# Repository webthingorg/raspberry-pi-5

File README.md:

📸 Raspberry Pi 5 Hardware

## Pictures

## Schematic

[PDF](raspberry-pi-5.pdf)

## Bill Of Materials

[Interactive BOM](https://gitlab.com/webthing.org/raspberry-pi-5/-/raw/main/raspberry-pi-5-bom.html?inline=false)

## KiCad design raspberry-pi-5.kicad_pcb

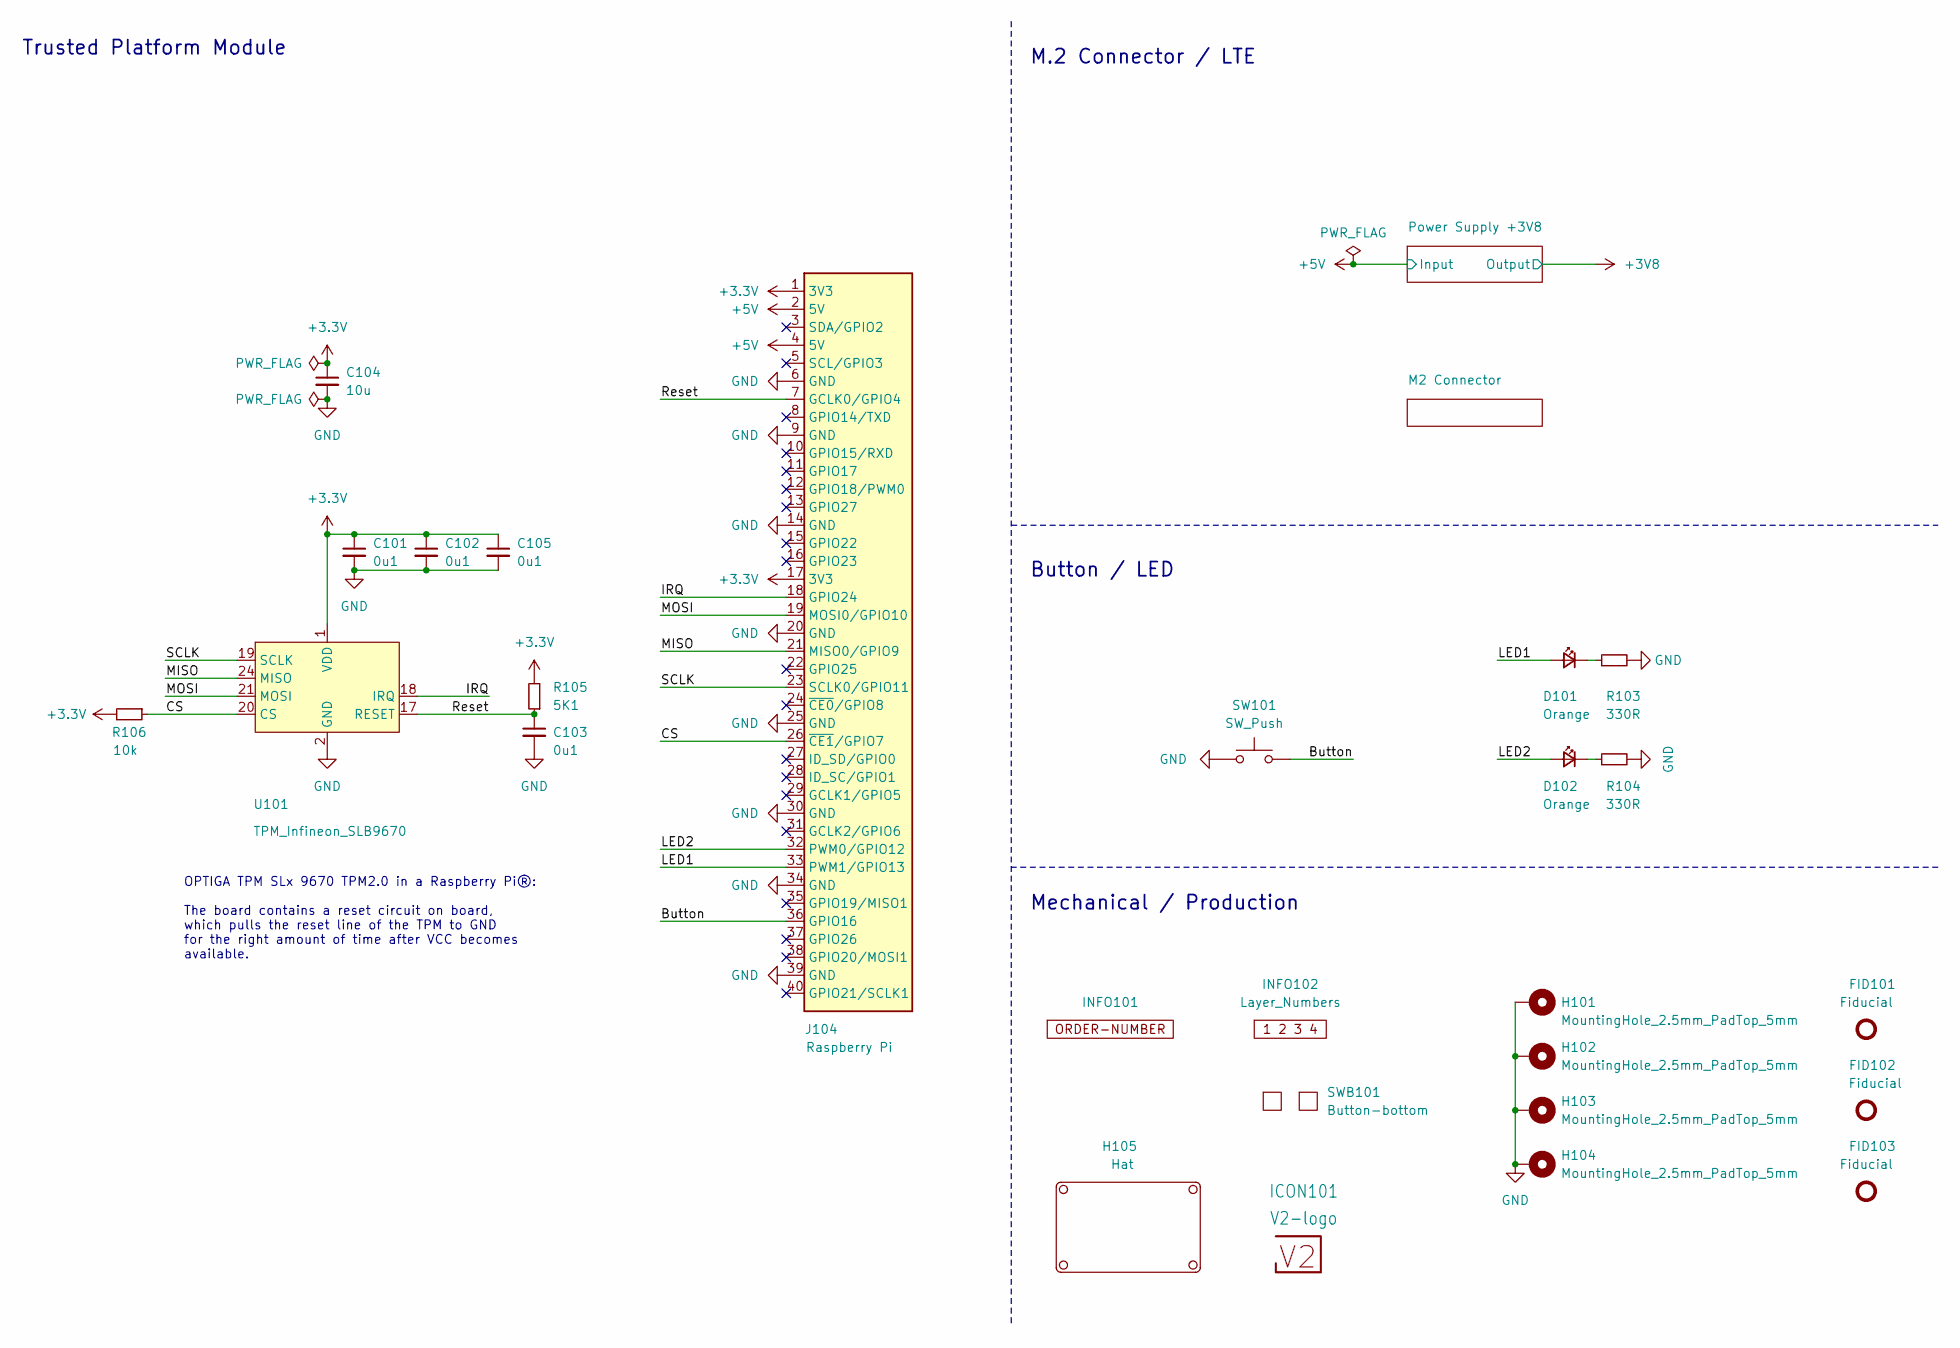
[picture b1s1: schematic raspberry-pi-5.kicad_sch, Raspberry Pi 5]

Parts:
C101, C102, C103, C105: 0u1; C_0603_1608Metric
C104: 10u; C_0603_1608Metric
D101, D102: Orange; LED_0603_1608Metric
FID101, FID102, FID103: Fiducial; Fiducial_0.5mm_Mask1mm_Paste
H101, H102, H103, H104: MountingHole_2.5mm_PadTop_5mm
H105: Hat
ICON101: V2-logo; Logo_Small
INFO101: ORDER-NUMBER; Order_Number
INFO102: Layer_Numbers
J104: Raspberry Pi; Connector
R103, R104: 330R; R_0603_1608Metric
R105: 5K1; R_0603_1608Metric
R106: 10k; R_0603_1608Metric
SW101: SW_Push; SKSG
SWB101: Button-bottom; PCB_Button-bottom
U101: TPM_Infineon_SLB9670; QFN-32-1EP_5x5mm_P0.5mm_EP3.6x3.6mm_ThermalVias

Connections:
+3.3V: C101.1, C102.1, C104.1, C105.1, J104.1 (3V3), J104.17 (3V3), R105.2, R106.2, U101.1 (VDD), U101.8 (VDD), U101.14 (VDD), U101.22 (VDD)
+5V: J104.2 (5V), J104.4 (5V); also elsewhere on the board
/Button: J104.36 (GPIO16), SW101.2
/CS: J104.26 (~CE1/GPIO7), R106.1, U101.20 (CS)
/IRQ: J104.18 (GPIO24), U101.18 (IRQ)
/LED1: D101.2 (A), J104.33 (PWM1/GPIO13)
/LED2: D102.2 (A), J104.32 (PWM0/GPIO12)
/MISO: J104.21 (MISO0/GPIO9), U101.24 (MISO)
/MOSI: J104.19 (MOSI0/GPIO10), U101.21 (MOSI)
/Reset: C103.1, J104.7 (GCLK0/GPIO4), R105.1, U101.17 (RESET)
/SCLK: J104.23 (SCLK0/GPIO11), U101.19 (SCLK)
GND: C101.2, C102.2, C103.2, C104.2, C105.2, H101.1, H102.1, H103.1, H104.1, J104.6 (GND), J104.9 (GND), J104.14 (GND), J104.20 (GND), J104.25 (GND), J104.30 (GND), J104.34 (GND), J104.39 (GND), R103.2, R104.2, SW101.1, U101.2 (GND), U101.9 (GND), U101.16 (GND), U101.23 (GND), U101.32 (GND), U101.33 (GND); also elsewhere on the board
unnamed: D101.1 (K), R103.1
unnamed: D102.1 (K), R104.1

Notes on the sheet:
Button / LED
Trusted Platform Module
Mechanical / Production
OPTIGA TPM SLx 9670 TPM2.0 in a Raspberry Pi®: The board contains a reset circuit on board, which pulls the reset line of the TPM to GND for the right amount of time after VCC becomes available.
M.2 Connector / LTE

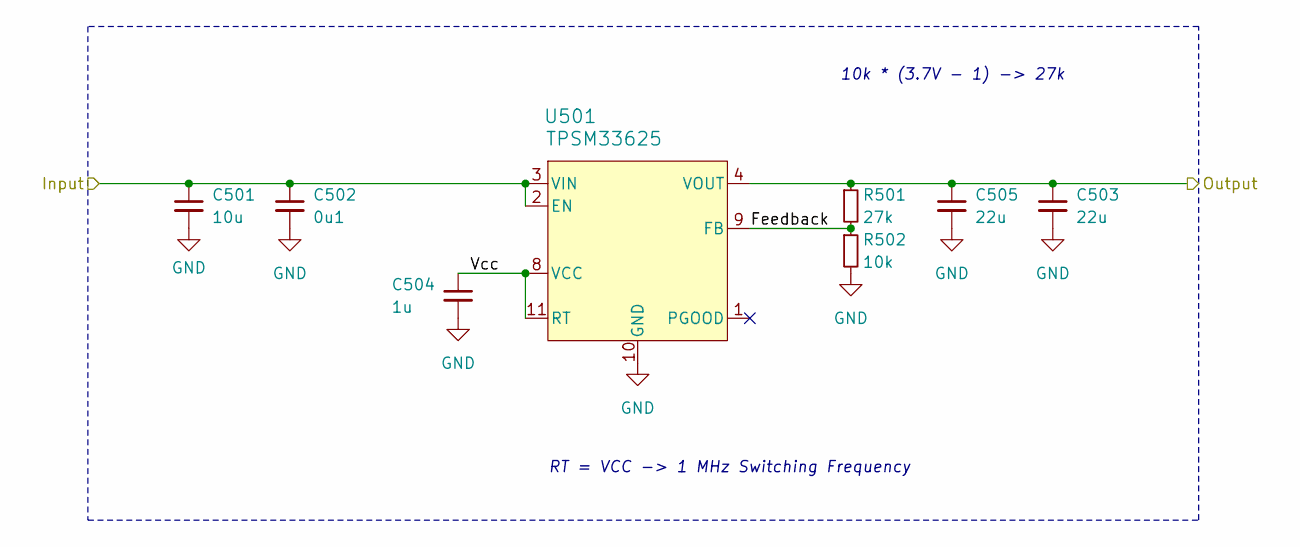
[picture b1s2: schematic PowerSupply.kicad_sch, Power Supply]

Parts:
C501: 10u; C_1210_3225Metric
C502: 0u1; C_0603_1608Metric
C503, C505: 22u; C_1210_3225Metric
C504: 1u; C_0603_1608Metric
R501: 27k; R_0603_1608Metric
R502: 10k; R_0603_1608Metric
U501: TPSM33625

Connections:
+3V8: C503.1, C505.1, R501.1, U501.4 (VOUT); also elsewhere on the board
+5V: C501.1, C502.1, U501.2 (EN), U501.3 (VIN); also elsewhere on the board
/Power Supply +3V8/Feedback: R501.2, R502.1, U501.9 (FB)
/Power Supply +3V8/Vcc: C504.1, U501.8 (VCC), U501.11 (RT)
GND: C501.2, C502.2, C503.2, C504.2, C505.2, R502.2, U501.10 (GND); also elsewhere on the board

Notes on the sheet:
10k * (3.7V - 1) -> 27k
RT = VCC -> 1 MHz Switching Frequency

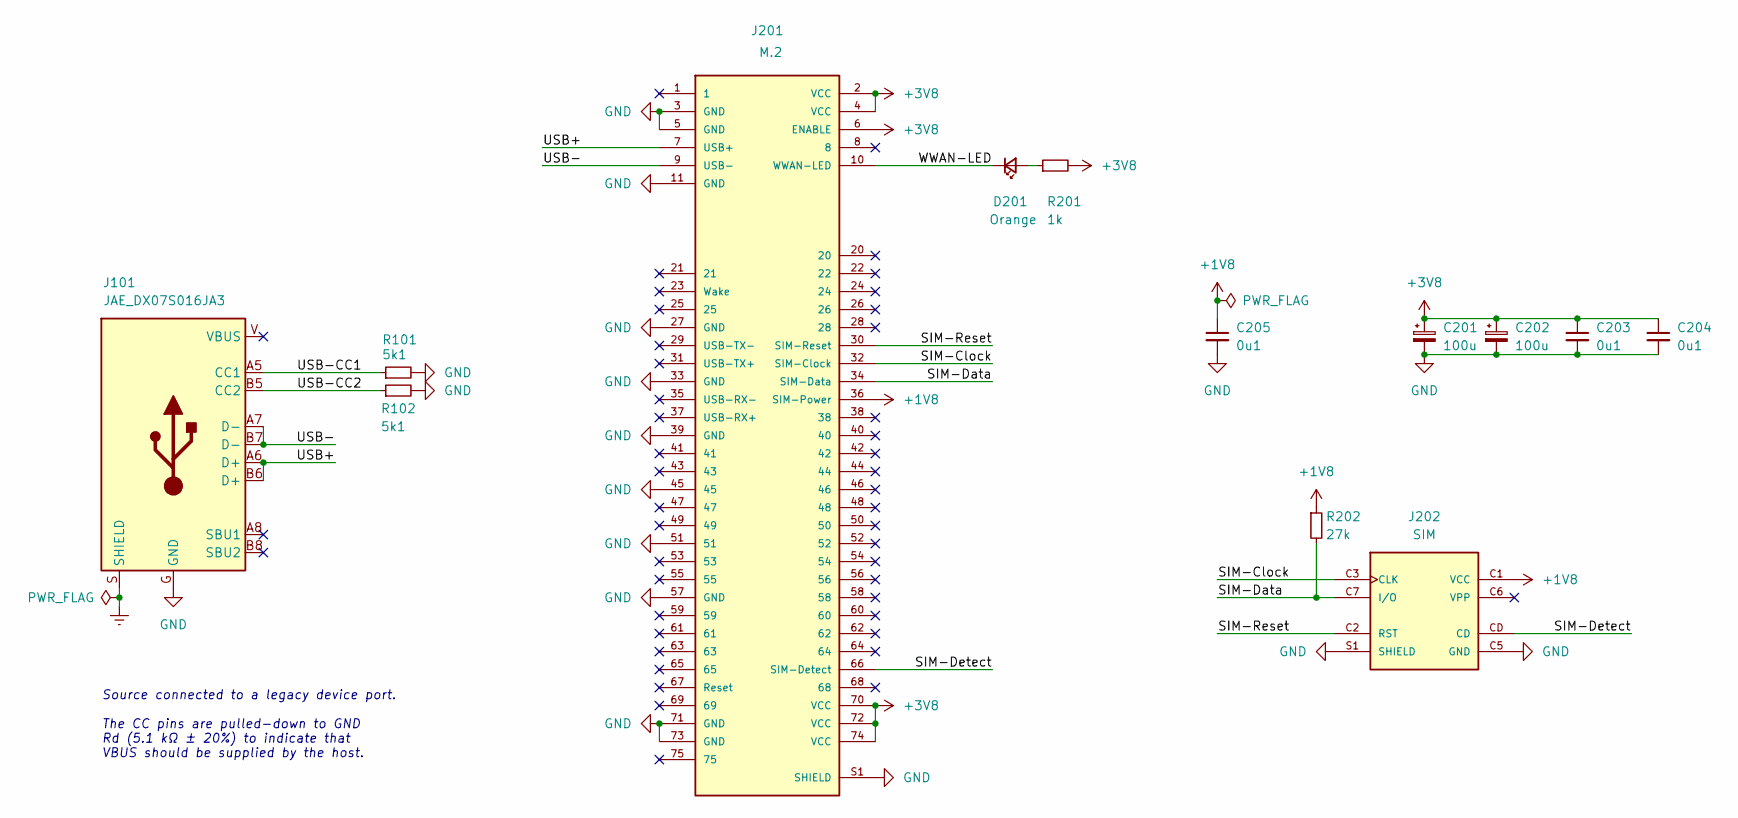
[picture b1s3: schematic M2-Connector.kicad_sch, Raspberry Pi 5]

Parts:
C201, C202: 100u; CP_EIA-3528-21_Kemet-B
C203, C204, C205: 0u1; C_0603_1608Metric
D201: Orange; LED_0603_1608Metric
J101: JAE_DX07S016JA3
J201: M.2; MDT180B01001
J202: SIM; Amphenol_G85D1171012HHR
R101, R102: 5k1; R_0603_1608Metric
R201: 1k; R_0603_1608Metric
R202: 27k; R_0603_1608Metric

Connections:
+1V8: C205.1, J201.36 (SIM-Power), J202.C1 (VCC), R202.1
+3V8: C201.1, C202.1, C203.1, C204.1, J201.2 (VCC), J201.4 (VCC), J201.6 (ENABLE), J201.70 (VCC), J201.72 (VCC), J201.74 (VCC), R201.2; also elsewhere on the board
/M2 Connector/SIM-Clock: J201.32 (SIM-Clock), J202.C3 (CLK)
/M2 Connector/SIM-Data: J201.34 (SIM-Data), J202.C7 (I/O), R202.2
/M2 Connector/SIM-Detect: J201.66 (SIM-Detect), J202.CD
/M2 Connector/SIM-Reset: J201.30 (SIM-Reset), J202.C2 (RST)
/M2 Connector/USB+: J101.A6 (D+), J101.B6 (D+), J201.7 (USB+)
/M2 Connector/USB-: J101.A7 (D-), J101.B7 (D-), J201.9 (USB-)
/M2 Connector/USB-CC1: J101.A5 (CC1), R101.1
/M2 Connector/USB-CC2: J101.B5 (CC2), R102.1
/M2 Connector/WWAN-LED: D201.1 (K), J201.10 (WWAN-LED)
Earth: J101.S (SHIELD)
GND: C201.2, C202.2, C203.2, C204.2, C205.2, J101.G (GND), J201.3 (GND), J201.5 (GND), J201.11 (GND), J201.27 (GND), J201.33 (GND), J201.39 (GND), J201.45, J201.51, J201.57 (GND), J201.71 (GND), J201.73 (GND), J201.S1 (SHIELD), J201.S2 (SHIELD), J201.SCREW (SHIELD), J202.C5 (GND), J202.S1 (SHIELD), J202.S2 (SHIELD), J202.S3 (SHIELD), J202.S4 (SHIELD), R101.2, R102.2; also elsewhere on the board
unnamed: D201.2 (A), R201.1

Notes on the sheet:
﻿Source connected to a legacy device port. The CC pins are pulled-down to GND Rd (5.1 kΩ ± 20%) to indicate that VBUS should be supplied by the host.

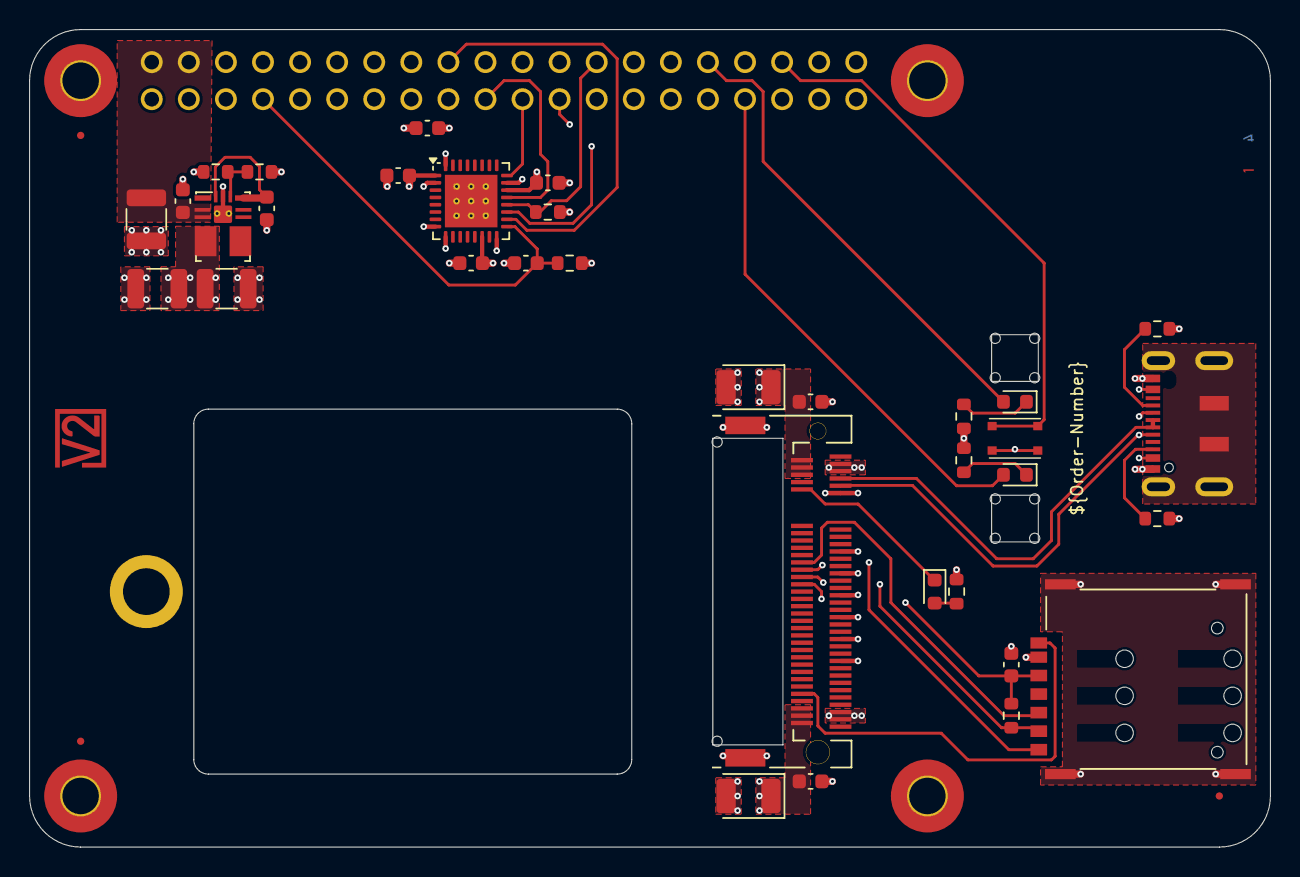
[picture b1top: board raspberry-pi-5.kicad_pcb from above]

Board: 4 copper layers, 85.0 x 56.0 mm, 47 parts (0 on the bottom side), 28 nets.

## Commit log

2024-09-26 Import
